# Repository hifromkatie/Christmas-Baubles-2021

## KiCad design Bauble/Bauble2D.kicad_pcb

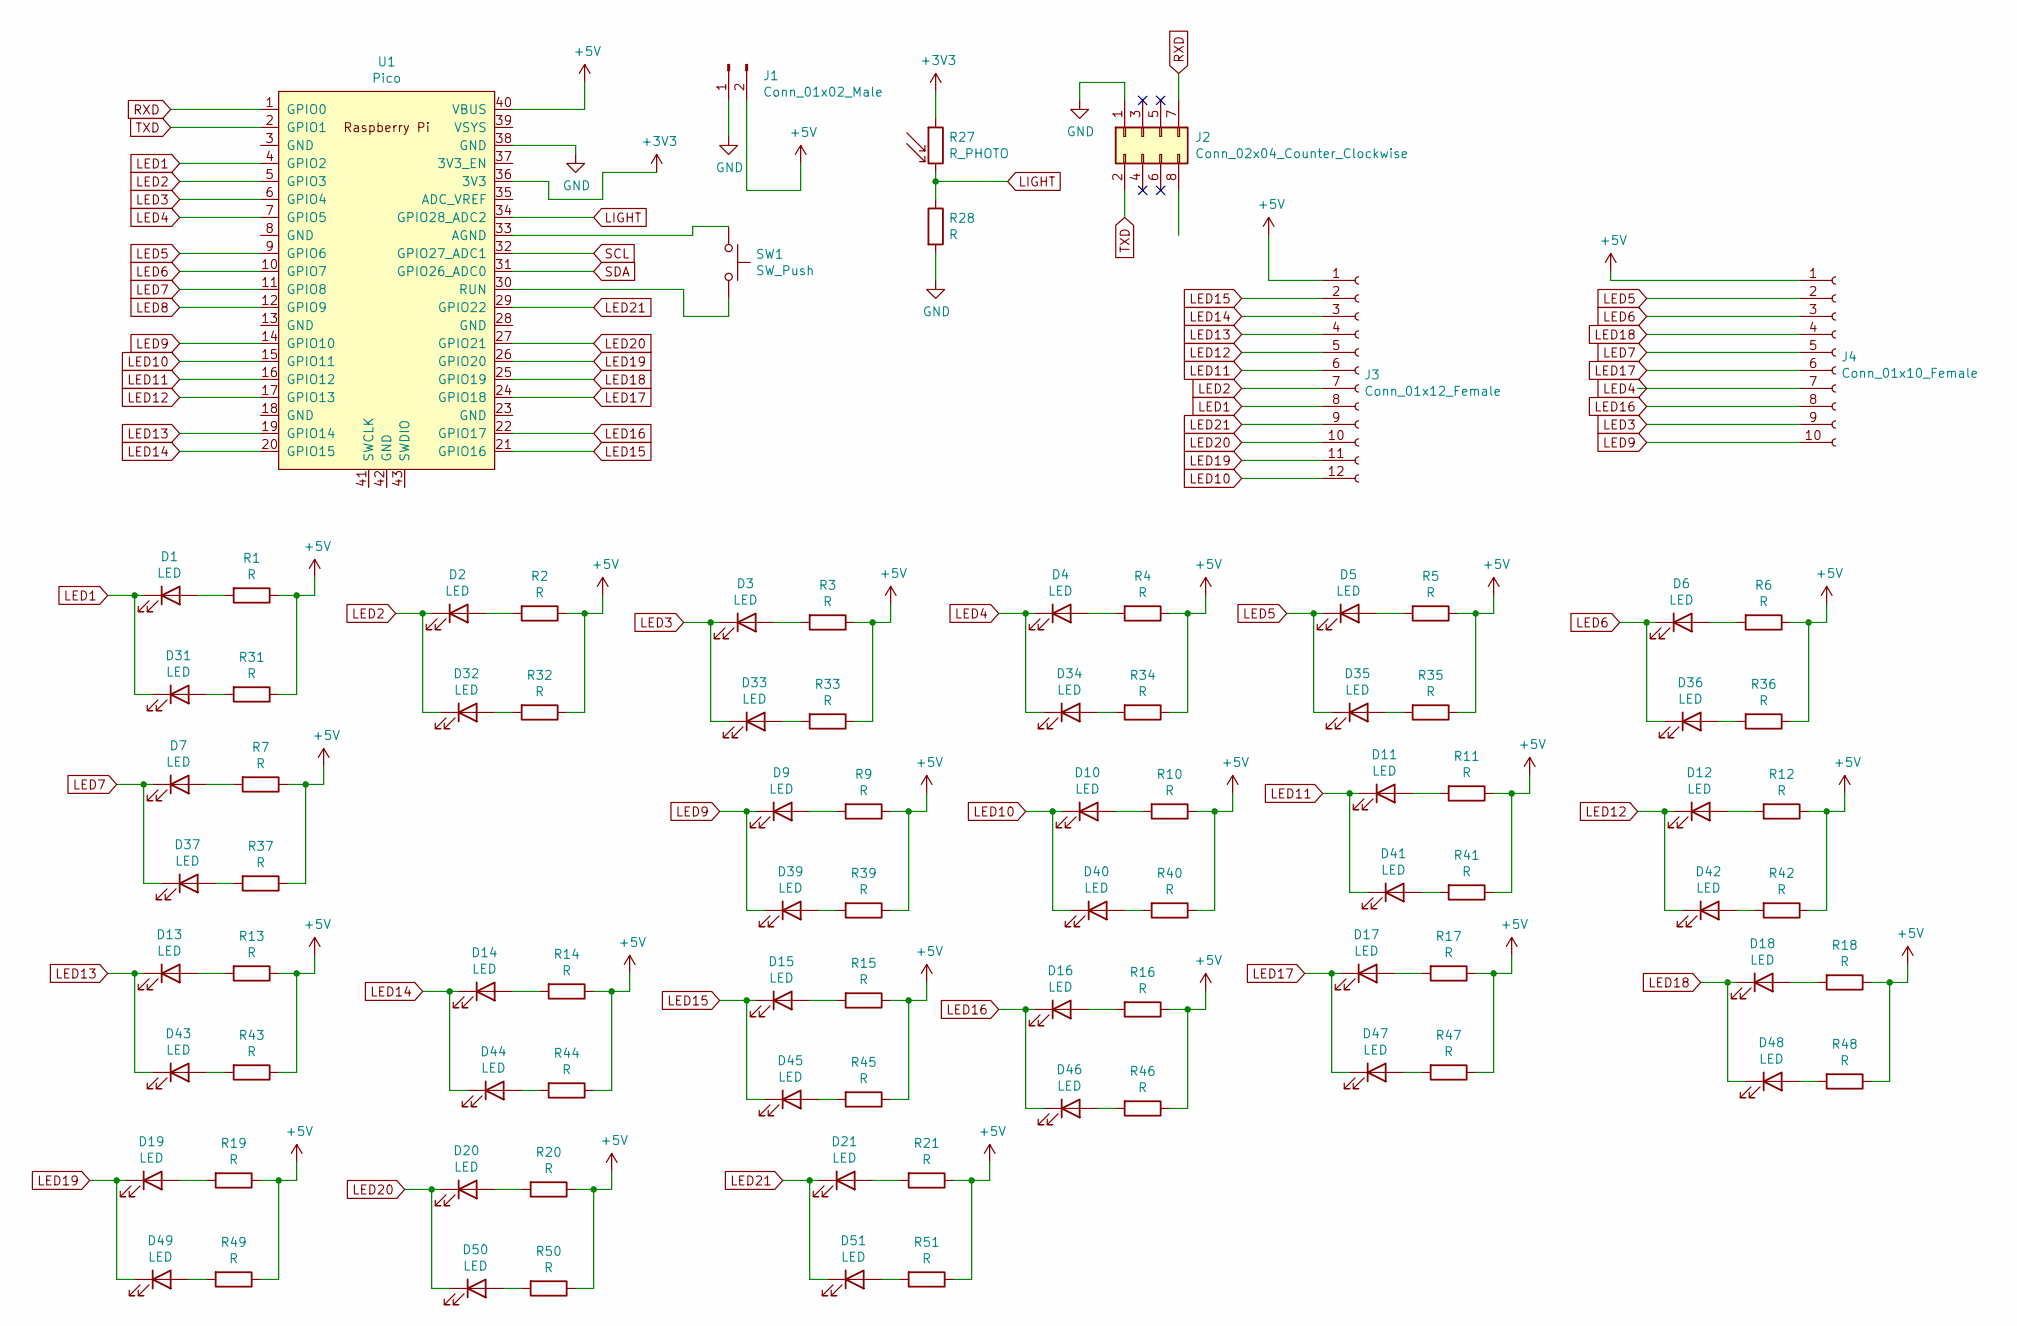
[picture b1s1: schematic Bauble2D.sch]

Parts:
D1, D2, D3, D4, D5, D6, D7, D9, D10, D11, D12, D13, D14, D15, D16, D17, D18, D19, D20, D21, D31, D32, D33, D34, D35, D36, D37, D39, D40, D41, D42, D43, D44, D45, D46, D47, D48, D49, D50, D51: LED; LED_0805_2012Metric_Pad1.15x1.40mm_HandSolder
J1: Conn_01x02_Male; Molex_KK-254_AE-6410-02A_1x02_P2.54mm_Vertical
J2: Conn_02x04_Counter_Clockwise; PinSocket_2x04_P2.54mm_Vertical
J3: Conn_01x12_Female; edge_connector-flat-12
J4: Conn_01x10_Female; edge_connector-flat-10
R1, R2, R3, R4, R5, R6, R7, R9, R10, R11, R12, R13, R14, R15, R16, R17, R18, R19, R20, R21, R28, R31, R32, R33, R34, R35, R36, R37, R39, R40, R41, R42, R43, R44, R45, R46, R47, R48, R49, R50, R51: R; R_0805_2012Metric_Pad1.20x1.40mm_HandSolder
R27: R_PHOTO; R_0805_2012Metric_Pad1.20x1.40mm_HandSolder
SW1: SW_Push; SW_SPST_CK_RS282G05A3
U1: Pico; RPi_Pico_SMD_TH

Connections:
+3V3: J2.8, R27.1, U1.36 (3V3)
+5V: J1.2, J3.1, J4.1, R1.1, R2.1, R3.1, R4.1, R5.1, R6.1, R7.1, R9.1, R10.1, R11.1, R12.1, R13.1, R14.1, R15.1, R16.1, R17.1, R18.1, R19.1, R20.1, R21.1, R31.1, R32.1, R33.1, R34.1, R35.1, R36.1, R37.1, R39.1, R40.1, R41.1, R42.1, R43.1, R44.1, R45.1, R46.1, R47.1, R48.1, R49.1, R50.1, R51.1, U1.40 (VBUS); also elsewhere on the board
GND: J1.1, J2.1, R28.2, U1.38 (GND)
LED1: D1.1 (K), D31.1 (K), J3.8, U1.4 (GPIO2)
LED2: D2.1 (K), D32.1 (K), J3.7, U1.5 (GPIO3)
LED3: D3.1 (K), D33.1 (K), J4.9, U1.6 (GPIO4)
LED4: D4.1 (K), D34.1 (K), J4.7, U1.7 (GPIO5)
LED5: D5.1 (K), D35.1 (K), J4.2, U1.9 (GPIO6)
LED6: D6.1 (K), D36.1 (K), J4.3, U1.10 (GPIO7)
LED7: D7.1 (K), D37.1 (K), J4.5, U1.11 (GPIO8)
LED8: U1.12 (GPIO9); also elsewhere on the board
LED9: D9.1 (K), D39.1 (K), J4.10, U1.14 (GPIO10)
LED10: D10.1 (K), D40.1 (K), J3.12, U1.15 (GPIO11)
LED11: D11.1 (K), D41.1 (K), J3.6, U1.16 (GPIO12)
LED12: D12.1 (K), D42.1 (K), J3.5, U1.17 (GPIO13)
LED13: D13.1 (K), D43.1 (K), J3.4, U1.19 (GPIO14)
LED14: D14.1 (K), D44.1 (K), J3.3, U1.20 (GPIO15)
LED15: D15.1 (K), D45.1 (K), J3.2, U1.21 (GPIO16)
LED16: D16.1 (K), D46.1 (K), J4.8, U1.22 (GPIO17)
LED17: D17.1 (K), D47.1 (K), J4.6, U1.24 (GPIO18)
LED18: D18.1 (K), D48.1 (K), J4.4, U1.25 (GPIO19)
LED19: D19.1 (K), D49.1 (K), J3.11, U1.26 (GPIO20)
LED20: D20.1 (K), D50.1 (K), J3.10, U1.27 (GPIO21)
LED21: D21.1 (K), D51.1 (K), J3.9, U1.29 (GPIO22)
LIGHT: R27.2, R28.1, U1.34 (GPIO28_ADC2)
unnamed: D1.2 (A), R1.2
unnamed: D2.2 (A), R2.2
unnamed: D3.2 (A), R3.2
unnamed: D4.2 (A), R4.2
unnamed: D5.2 (A), R5.2
unnamed: D6.2 (A), R6.2
unnamed: D7.2 (A), R7.2
unnamed: D9.2 (A), R9.2
unnamed: D10.2 (A), R10.2
unnamed: D11.2 (A), R11.2
unnamed: D12.2 (A), R12.2
unnamed: D13.2 (A), R13.2
unnamed: D14.2 (A), R14.2
unnamed: D15.2 (A), R15.2
unnamed: D16.2 (A), R16.2
unnamed: D17.2 (A), R17.2
unnamed: D18.2 (A), R18.2
unnamed: D19.2 (A), R19.2
unnamed: D20.2 (A), R20.2
unnamed: D21.2 (A), R21.2
unnamed: D31.2 (A), R31.2
unnamed: D32.2 (A), R32.2
unnamed: D33.2 (A), R33.2
unnamed: D34.2 (A), R34.2
unnamed: D35.2 (A), R35.2
unnamed: D36.2 (A), R36.2
unnamed: D37.2 (A), R37.2
unnamed: D39.2 (A), R39.2
unnamed: D40.2 (A), R40.2
unnamed: D41.2 (A), R41.2
unnamed: D42.2 (A), R42.2
unnamed: D43.2 (A), R43.2
unnamed: D44.2 (A), R44.2
unnamed: D45.2 (A), R45.2
unnamed: D46.2 (A), R46.2
unnamed: D47.2 (A), R47.2
unnamed: D48.2 (A), R48.2
unnamed: D49.2 (A), R49.2
unnamed: D50.2 (A), R50.2
unnamed: D51.2 (A), R51.2
unnamed: SW1.1, U1.33 (AGND)
unnamed: SW1.2, U1.30 (RUN)
RXD: J2.7, U1.1 (GPIO0)
SCL: U1.32 (GPIO27_ADC1)
SDA: U1.31 (GPIO26_ADC0)
TXD: J2.2, U1.2 (GPIO1)

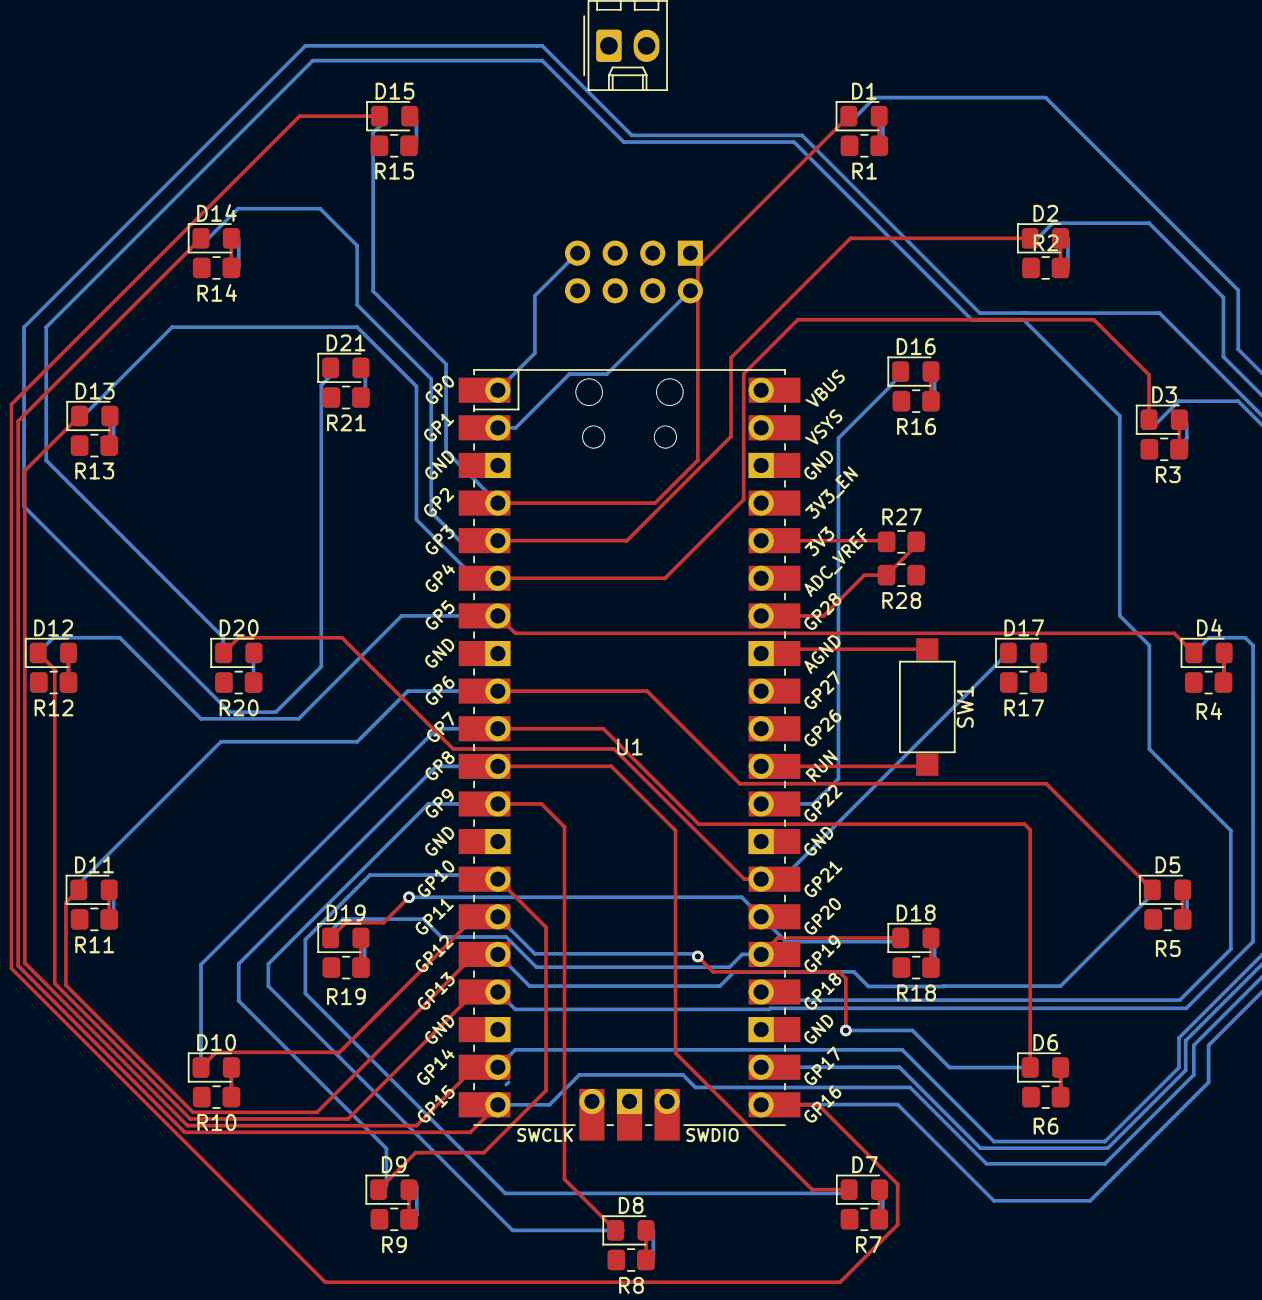
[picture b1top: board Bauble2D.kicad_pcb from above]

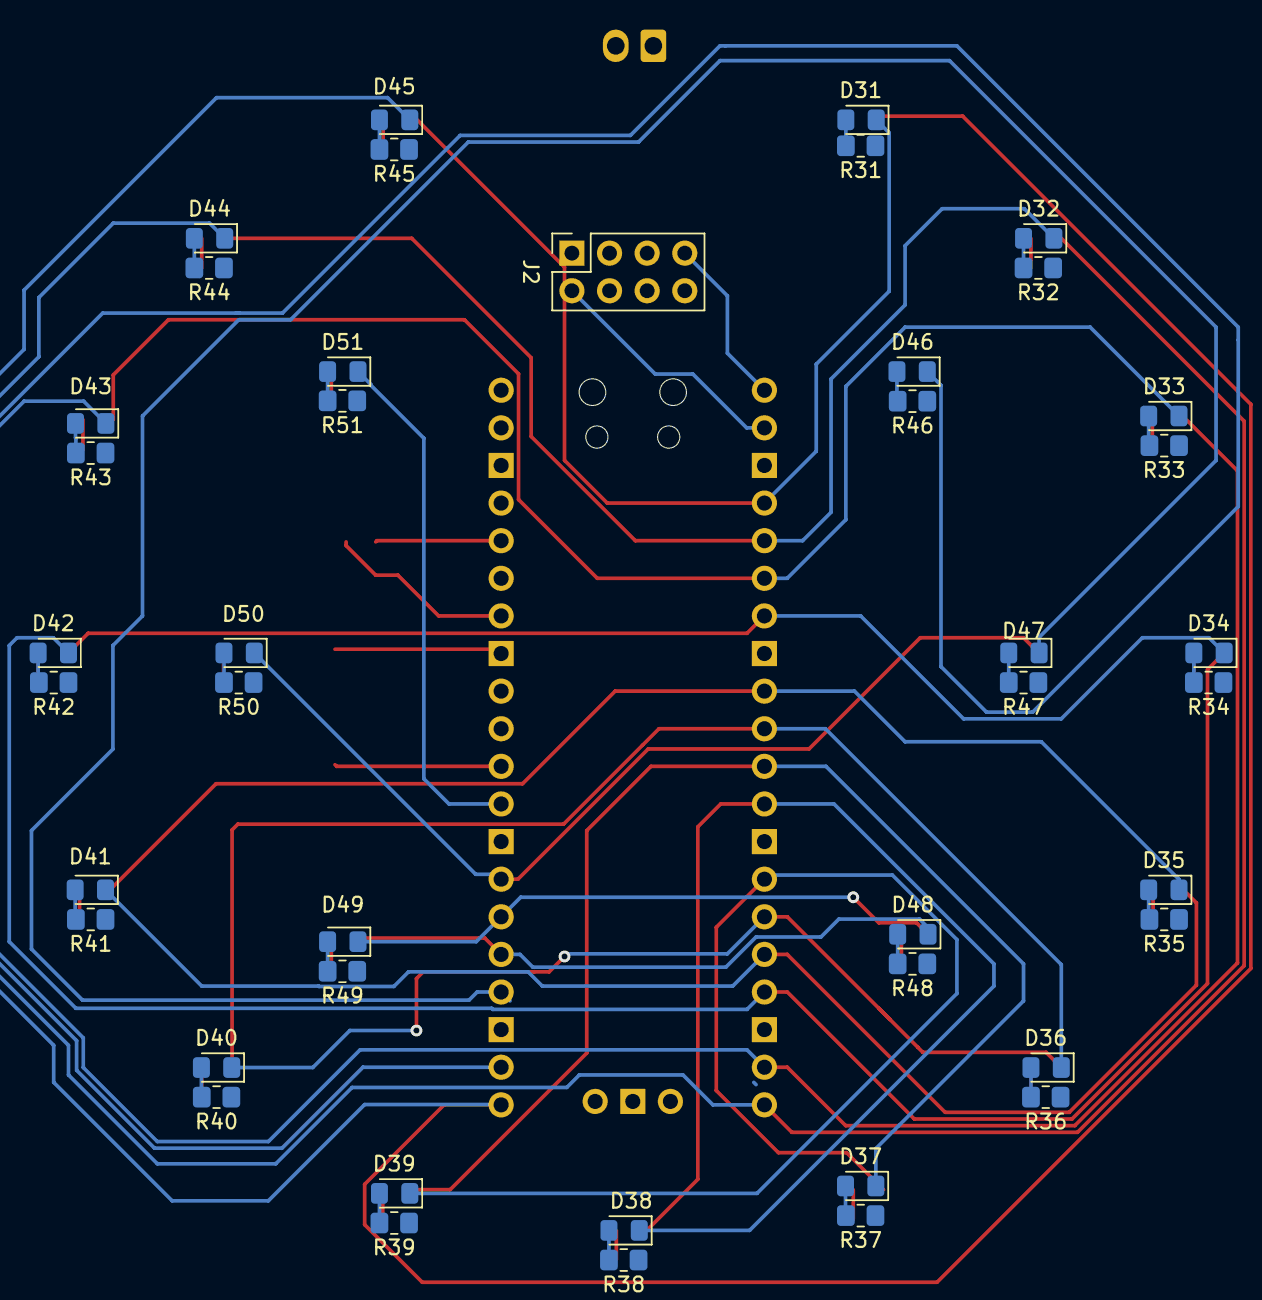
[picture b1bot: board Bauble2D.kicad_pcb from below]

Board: 2 copper layers, 90 parts (43 on the bottom side), 71 nets.

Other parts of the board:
D8, D38: LED; LED_0805_2012Metric_Pad1.15x1.40mm_HandSolder
R8, R38: R; R_0805_2012Metric_Pad1.20x1.40mm_HandSolder

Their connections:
+5V: R8.1, R38.1; also elsewhere on the board
LED8: D8.1, D38.1; also elsewhere on the board
unnamed: D8.2, R8.2
unnamed: D38.2, R38.2
